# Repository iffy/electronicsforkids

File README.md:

The directories above contain some fun electronics projects for kids (or anyone that wants to do some electronic stuff).

# How to get stuff

- I've ordered PCBs from [oshpark.com](https://oshpark.com/).
- I've ordered parts (everything that goes on the board) from [Mouser](https://www.mouser.com/)
- Projects include a `bom.txt` file which you can upload to Mouser when ordering parts.
- If you need a soldering iron, this one looks like a really good deal: [https://amzn.com/B06XZ31W3M](https://amzn.com/B06XZ31W3M)

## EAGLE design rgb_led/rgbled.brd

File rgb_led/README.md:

This circuit board has three knobs (pots) and one red, green, blue LED.  Turning the knobs adjusts the amount of red/green/blue emitted.

# How to orient the LED

The anode of the LED attaches to the top-right pad.  There ought to be two white lines around the anode pad.  When looking at the LED, look for a little L shape inside--that's the red corner which goes to the bottom right.

The white arrow here is pointing to the anode pad:

# How to solder the tiny LED

It's pretty tricky to solder the LED, but it can be done.  Put a little solder on *one* pad.  Next hold the LED in place on the solder then place the iron on the pad to melt the solder and let the LED sink into place.  Pull the iron away and then let go of the LED.  The other 3 pads should be easier :)

# Which resistor goes where?

There are 3 required resistors.  Here are their values:

| Name | Value |
|---|---|
| RRED | 100 Ohm |
| RGRN | 60 Ohm |
| RBLU | 60 Ohm |

There are 3 optional resistors that, if present, will remove a lot of the "dead space" when turning the knobs.

| Name | Value |
|---|---|
| RRP | ~453 Ohm |
| RGP | ~422 Ohm |
| RBP | 300 Ohm |

# Battery

This takes a single CR2032 battery.

# Improvements

Things I'd like to do if I redesign it:

- Find physically smaller pots.  They're disproportionally huge.
- Use a button instead of a switch (so they don't die).

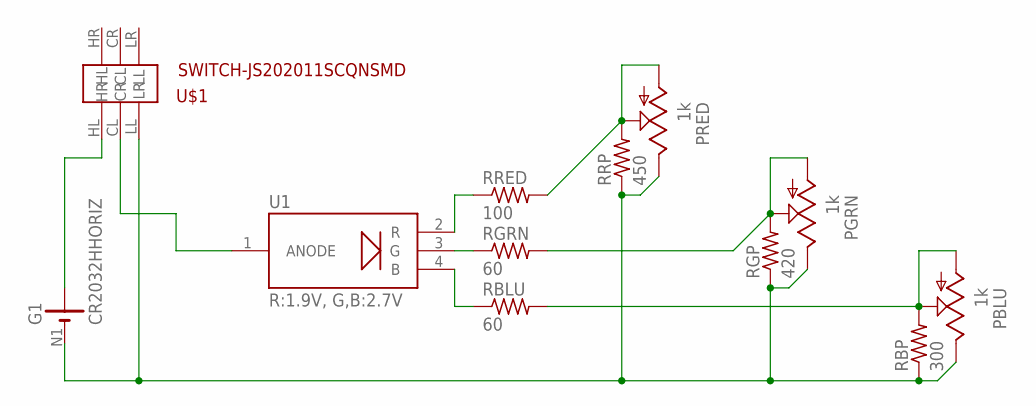
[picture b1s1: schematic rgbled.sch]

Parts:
G1: CR2032HHORIZ; LINX-BAT-HLD-001
PBLU: 1k; PTV111-1
PGRN: 1k; PTV111-1
PRED: 1k; PTV111-1
RBLU: 60; M0805
RBP: 300; R0805
RGP: 420; R0805
RGRN: 60; M0805
RRED: 100; M0805
RRP: 450; R0805
U1: R:1.9V, G,B:2.7V; LRTB_R48G
U$1: SWITCH-JS202011SCQNSMD; SWITCH-JS202011CQN

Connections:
unnamed: U1.1 (ANODE), U$1.CL
unnamed: RRED.1, U1.2 (R)
unnamed: RGRN.1, U1.3 (G)
unnamed: RBLU.1, U1.4 (B)
unnamed: PGRN.2 (S), PGRN.3 (A), RGP.2, RGRN.2
unnamed: PBLU.2 (S), PBLU.3 (A), RBLU.2, RBP.2
unnamed: G1.P@1 (+), G1.P@2 (+), U$1.HL
unnamed: G1.N1 (-), PBLU.1 (E), PGRN.1 (E), PRED.1 (E), RBP.1, RGP.1, RRP.1, U$1.LL
RRP: PRED.2 (S), PRED.3 (A), RRED.2, RRP.2

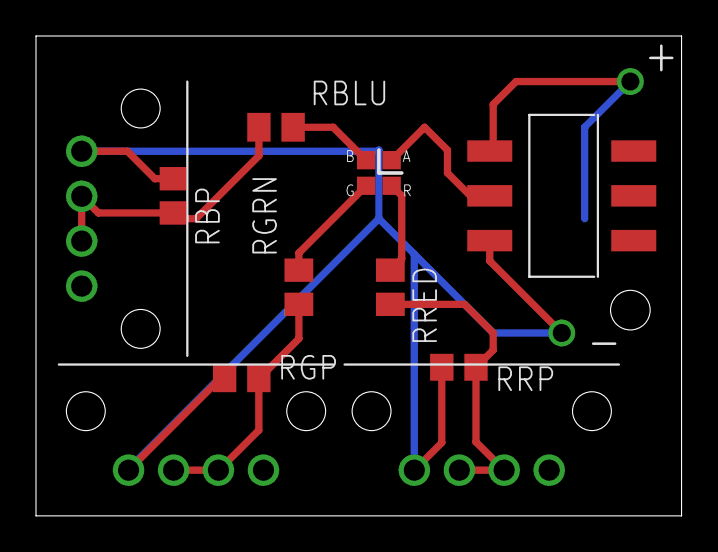
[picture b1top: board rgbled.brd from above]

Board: 2 copper layers, 35.9 x 26.7 mm, 12 parts (1 on the bottom side), 9 nets.

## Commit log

2017-11-09 Add RGB LED project
2017-11-09 Links to where to get stuff
2017-11-09 update resisotr instructions
2017-11-09 Another pic
2017-11-09 show anode
2017-11-09 Knob size
2017-11-09 better intro
2017-11-20 New version of rgbled
2017-11-20 Fix table
2017-11-20 Add battery
